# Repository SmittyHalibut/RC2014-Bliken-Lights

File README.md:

# RC2014-Bliken-Lights
A Blinken Lights front panel for the RC2014.

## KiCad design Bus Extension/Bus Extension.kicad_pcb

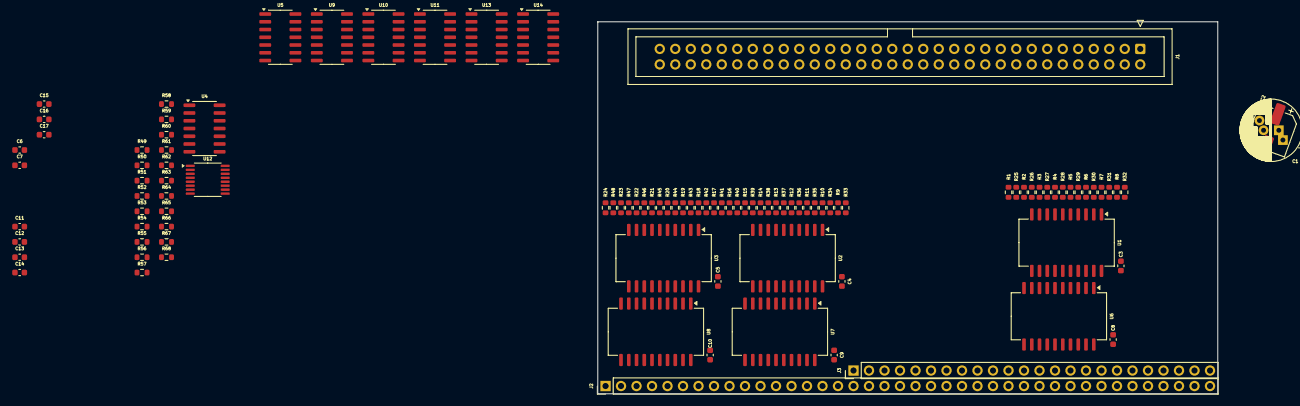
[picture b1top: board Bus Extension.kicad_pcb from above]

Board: 2 copper layers, 101.6 x 61.0 mm, 102 parts (0 on the bottom side), 146 nets, no tracks yet.

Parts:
C1: 100uF; CP_Radial_D10.0mm_P2.50mm_P5.00mm
C2: 100uF; CP_Elec_6.3x5.4
C3, C4, C5, C6, C7, C8, C9, C10, C11, C12, C13, C14, C15, C16, C17: 1uF; C_0603_1608Metric
J1: Conn_02x32_Row_Letter_First; IDC-Header_2x32_P2.54mm_Vertical
J2: Conn_01x40; PinHeader_1x40_P2.54mm_Vertical
J3: Conn_01x24; PinHeader_1x24_P2.54mm_Vertical
R1, R2, R3, R4, R5, R6, R7, R8, R9, R10, R11, R12, R13, R14, R15, R16, R17, R18, R19, R20, R21, R22, R23, R24, R49, R50, R51, R52, R53, R54, R55, R56, R57, R58, R59, R60: 470R; R_0603_1608Metric
R25, R26, R27, R28, R29, R30, R31, R32, R33, R34, R35, R36, R37, R38, R39, R40, R41, R42, R43, R44, R45, R46, R47, R48, R61, R62, R63, R64, R65, R66, R67, R68: 10k; R_0603_1608Metric
U1, U2, U3, U6, U7, U8: 74HCT244; SOIC-20W_7.5x15.4mm_P1.27mm
U4, U5: 74HCT02; SOIC-14_3.9x8.7mm_P1.27mm
U9, U10: 74HCT04; SOIC-14_3.9x8.7mm_P1.27mm
U11: 74HC74; SOIC-14_3.9x8.7mm_P1.27mm
U12: 74HC123; TSSOP-16_4.4x5mm_P0.65mm
U13, U14: 74LS125; SOIC-14_3.9x8.7mm_P1.27mm

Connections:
+5V: C1.1, C2.1, C3.1, C4.1, C5.1, C6.1, C7.1, C8.1, C9.1, C10.1, C11.1, C12.1, C13.1, C15.1, C16.1, C17.1, J2.18, J3.2, R25.2, R26.2, R27.2, R28.2, R29.2, R30.2, R31.2, R32.2, R33.2, R34.2, R35.2, R36.2, R37.2, R38.2, R39.2, R40.2, R41.2, R42.2, R43.2, R44.2, R45.2, R46.2, R47.2, R48.2, R49.1, R61.2, R62.2, R63.2, R64.2, R65.2, R66.2, R67.2, R68.1, U1.20 (VCC), U2.20 (VCC), U3.20 (VCC), U4.14 (VCC), U5.14 (VCC), U6.20 (VCC), U7.20 (VCC), U8.20 (VCC), U9.14 (VCC), U10.14 (VCC), U11.2 (D), U11.4 (~S), U11.14 (VCC), U12.10 (B), U12.11 (Clr), U12.16 (VCC), U13.14 (VCC), U14.14 (VCC)
/A0: J2.16, U2.2 (1A0), U7.18 (1Y0)
/A1: J2.15, U2.17 (2A0), U7.3 (2Y0)
/A2: J2.14, U2.4 (1A1), U7.16 (1Y1)
/A3: J2.13, U2.15 (2A1), U7.5 (2Y1)
/A4: J2.12, U2.6 (1A2), U7.14 (1Y2)
/A5: J2.11, U2.13 (2A2), U7.7 (2Y2)
/A6: J2.10, U2.8 (1A3), U7.12 (1Y3)
/A7: J2.9, U2.11 (2A3), U7.9 (2Y3)
/A8: J2.8, U3.2 (1A0), U8.18 (1Y0)
/A9: J2.7, U3.17 (2A0), U8.3 (2Y0)
/A10: J2.6, U3.4 (1A1), U8.16 (1Y1)
/A11: J2.5, U3.15 (2A1), U8.5 (2Y1)
/A12: J2.4, U3.6 (1A2), U8.14 (1Y2)
/A13: J2.3, U3.13 (2A2), U8.7 (2Y2)
/A14: J2.2, U3.8 (1A3), U8.12 (1Y3)
/A15: J2.1, U3.11 (2A3), U8.9 (2Y3)
/BUSAK: U5.3, U9.1
/BUSRQ: J3.8, U13.3
/BUSRQSW: J1.48, R64.1, U5.2, U13.1
/D0: J2.27, U1.11 (2A3), U6.9 (2Y3)
/D1: J2.28, U1.8 (1A3), U6.12 (1Y3)
/D2: J2.29, U1.13 (2A2), U6.7 (2Y2)
/D3: J2.30, U1.6 (1A2), U6.14 (1Y2)
/D4: J2.31, U1.15 (2A1), U6.5 (2Y1)
/D5: J2.32, U1.4 (1A1), U6.16 (1Y1)
/D6: J2.33, U1.17 (2A0), U6.3 (2Y0)
/D7: J2.34, U1.2 (1A0), U6.18 (1Y0)
/DBUSSW: J1.52, R61.1, U5.8
/DBUS_EN: U5.10, U9.13, U13.4
/HALT: J3.7, U9.3
/HAVEBUS: U5.1, U10.5
/LED A0: J1.3, R9.2
/LED A1: J1.7, R10.2
/LED A2: J1.11, R11.2
/LED A3: J1.15, R12.2
/LED A4: J1.19, R13.2
/LED A5: J1.23, R14.2
/LED A6: J1.27, R15.2
/LED A7: J1.31, R16.2
/LED A8: J1.33, R17.2
/LED A9: J1.37, R18.2
/LED A10: J1.41, R19.2
/LED A11: J1.45, R20.2
/LED A12: J1.49, R21.2
/LED A13: J1.53, R22.2
/LED A14: J1.57, R23.2
/LED A15: J1.61, R24.2
/LED D0: J1.2, R1.2
/LED D1: J1.4, R2.2
/LED D2: J1.6, R3.2
/LED D3: J1.8, R4.2
/LED D4: J1.10, R5.2
/LED D5: J1.12, R6.2
/LED D6: J1.14, R7.2
/LED D7: J1.16, R8.2
/LED IORD: J1.38, R53.2
/LED IOWR: J1.40, R54.2
/LED MEMRD: J1.34, R51.2
/LED MEMRW: J1.36, R52.2
/LED Power: J1.60, R49.2
/LED ~BUSAK: J1.46, R50.2
/LED ~HALT: J1.42, R56.2
/LED ~WAIT: J1.44, R55.2
/M1: J2.19, U12.9 (A)
/MEMIOSW: J1.54, R62.1, U10.13, U14.2
/Reset: J1.62, J2.20, R65.1
/SINGLESW: J1.56, R63.1, U5.11
/STEPSW: J1.58, R66.1, U11.3 (C)
/SW A0: J1.1, R33.1, U7.2 (1A0)
/SW A1: J1.5, R34.1, U7.17 (2A0)
/SW A2: J1.9, R35.1, U7.4 (1A1)
/SW A3: J1.13, R36.1, U7.15 (2A1)
/SW A4: J1.17, R37.1, U7.6 (1A2)
/SW A5: J1.21, R38.1, U7.13 (2A2)
/SW A6: J1.25, R39.1, U7.8 (1A3)
/SW A7: J1.29, R40.1, U7.11 (2A3)
/SW A8: J1.35, R41.1, U8.2 (1A0)
/SW A9: J1.39, R42.1, U8.17 (2A0)
/SW A10: J1.43, R43.1, U8.4 (1A1)
/SW A11: J1.47, R44.1, U8.15 (2A1)
/SW A12: J1.51, R45.1, U8.6 (1A2)
/SW A13: J1.55, R46.1, U8.13 (2A2)
/SW A14: J1.59, R47.1, U8.8 (1A3)
/SW A15: J1.63, R48.1, U8.11 (2A3)
/SW D0: J1.18, R25.1, U6.11 (2A3)
/SW D1: J1.20, R26.1, U6.8 (1A3)
/SW D2: J1.22, R27.1, U6.13 (2A2)
/SW D3: J1.24, R28.1, U6.6 (1A2)
/SW D4: J1.26, R29.1, U6.15 (2A1)
/SW D5: J1.28, R30.1, U6.4 (1A1)
/SW D6: J1.30, R31.1, U6.17 (2A0)
/SW D7: J1.32, R32.1, U6.2 (1A0)
/SW WRITE: J1.50, R67.1, U5.5
/WAIT: U9.5, U13.11
/WAITING: U10.8, U13.13
/WRITING: U5.4, U10.11
/~BUSAK: R50.1, U9.2
/~DBUS_EN: U5.6, U6.1 (1OE), U6.19 (2OE), U9.12
/~HALT: R56.1, U9.4
/~HAVEBUS: U5.9, U7.1 (1OE), U7.19 (2OE), U8.1 (1OE), U8.19 (2OE), U10.6, U14.1, U14.4
/~MEMIOSW: U10.12, U14.5
/~RX2: R60.1, U10.4
/~RX: R58.1, U9.10
/~TX2: R59.1, U10.2
/~TX: R57.1, U9.8
/~WAIT: R55.1, U9.6
/~WRITING: U10.10, U13.10
GND: C1.2, C2.2, C3.2, C4.2, C5.2, C6.2, C7.2, C8.2, C9.2, C10.2, C11.2, C12.2, C13.2, C15.2, C16.2, C17.2, J1.64, J2.17, J3.1, U1.1 (1OE), U1.10 (GND), U1.19 (2OE), U2.1 (1OE), U2.10 (GND), U2.19 (2OE), U3.1 (1OE), U3.10 (GND), U3.19 (2OE), U4.7 (GND), U5.7 (GND), U6.10 (GND), U7.10 (GND), U8.10 (GND), U9.7 (GND), U10.7 (GND), U11.7 (GND), U12.8 (GND), U13.2, U13.5, U13.7 (GND), U13.9, U13.12, U14.7 (GND), U14.9, U14.10, U14.12, U14.13
IORD: R53.1, U4.10
IORQ: J2.26, U4.8, U4.11, U14.6
IOWR: R54.1, U4.13
MEMRD: R51.1, U4.1
MEMWR: R52.1, U4.4
MREQ: U4.2, U4.5, U14.3
unnamed: R8.1, U1.18 (1Y0)
unnamed: R6.1, U1.16 (1Y1)
unnamed: R4.1, U1.14 (1Y2)
unnamed: R2.1, U1.12 (1Y3)
unnamed: R7.1, U1.3 (2Y0)
unnamed: R5.1, U1.5 (2Y1)
unnamed: R3.1, U1.7 (2Y2)
unnamed: R1.1, U1.9 (2Y3)
unnamed: R9.1, U2.18 (1Y0)
unnamed: R11.1, U2.16 (1Y1)
unnamed: R13.1, U2.14 (1Y2)
unnamed: R15.1, U2.12 (1Y3)
unnamed: R10.1, U2.3 (2Y0)
unnamed: R12.1, U2.5 (2Y1)
unnamed: R14.1, U2.7 (2Y2)
unnamed: R16.1, U2.9 (2Y3)
unnamed: R17.1, U3.18 (1Y0)
unnamed: R19.1, U3.16 (1Y1)
unnamed: R21.1, U3.14 (1Y2)
unnamed: R23.1, U3.12 (1Y3)
unnamed: R18.1, U3.3 (2Y0)
unnamed: R20.1, U3.5 (2Y1)
unnamed: R22.1, U3.7 (2Y2)
unnamed: R24.1, U3.9 (2Y3)
unnamed: U5.13, U10.9
unnamed: U5.12, U11.5 (Q)
unnamed: U11.1 (~R), U12.12 (~Q)
unnamed: C14.2, U12.6 (Cext)
unnamed: C14.1, R68.2, U12.7 (RCext)
RD: U4.3, U4.9, U13.6
WR: U4.6, U4.12, U13.8

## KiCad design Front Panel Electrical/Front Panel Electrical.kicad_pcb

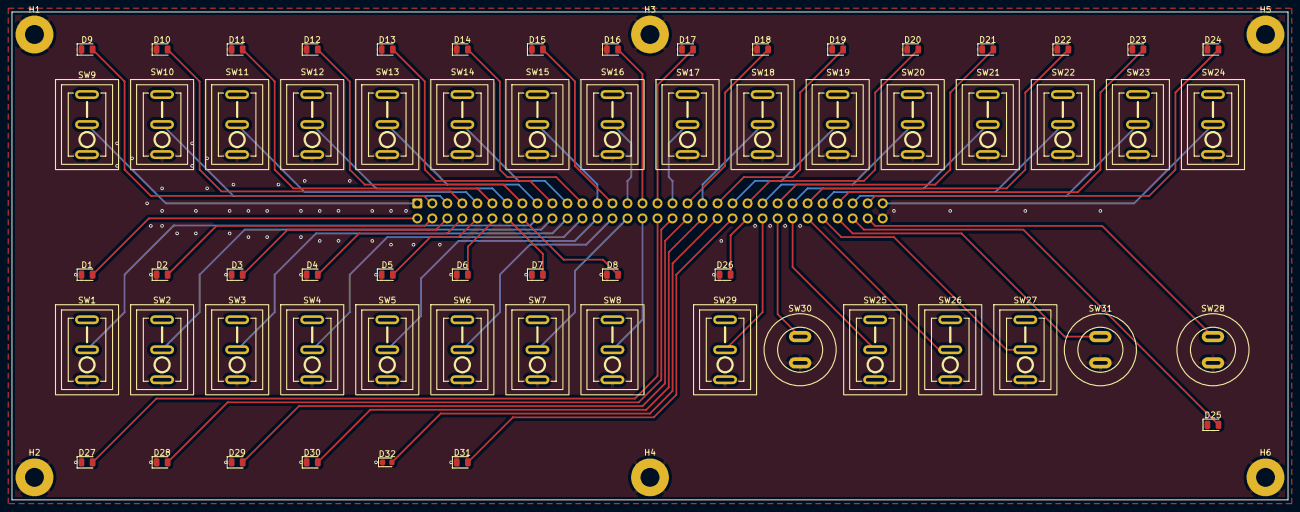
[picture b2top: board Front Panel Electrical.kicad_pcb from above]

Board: 2 copper layers, 215.9 x 82.6 mm, 70 parts (1 on the bottom side), 64 nets.

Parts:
D1, D2, D3, D4, D5, D6, D7, D8, D9, D10, D11, D12, D13, D14, D15, D16, D17, D18, D19, D20, D21, D22, D23, D24, D26, D27, D28, D29, D30, D31: Yellow; LED_0805_2012Metric
D25: Green; LED_0805_2012Metric
D32: Red LED; LED_0603_1608Metric
H1, H2, H3, H4, H5, H6: MountingHole_Pad; MountingHole_3.2mm_M3_Pad
J2: Conn_02x32_Row_Letter_First; IDC-Header_2x32_P2.54mm_Vertical
SW1, SW2, SW3, SW4, SW9, SW10, SW11, SW12, SW17, SW18, SW19, SW20: Black; Switch_Rocker_SPDT_15x10mm
SW5, SW6, SW7, SW8, SW13, SW14, SW15, SW16, SW21, SW22, SW23, SW24: Red; Switch_Rocker_SPDT_15x10mm
SW25, SW26, SW27, SW29: Switch; Switch_Rocker_SPDT_15x10mm
SW28, SW30, SW31: Button; Switch_Pushbutton_SPST_12mm

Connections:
/LED A0: D9.2 (A), J2.3
/LED A1: D10.2 (A), J2.7
/LED A2: D11.2 (A), J2.11
/LED A3: D12.2 (A), J2.15
/LED A4: D13.2 (A), J2.19
/LED A5: D14.2 (A), J2.23
/LED A6: D15.2 (A), J2.27
/LED A7: D16.2 (A), J2.31
/LED A8: D17.2 (A), J2.33
/LED A9: D18.2 (A), J2.37
/LED A10: D19.2 (A), J2.41
/LED A11: D20.2 (A), J2.45
/LED A12: D21.2 (A), J2.49
/LED A13: D22.2 (A), J2.53
/LED A14: D23.2 (A), J2.57
/LED A15: D24.2 (A), J2.61
/LED D0: D1.2 (A), J2.2
/LED D1: D2.2 (A), J2.4
/LED D2: D3.2 (A), J2.6
/LED D3: D4.2 (A), J2.8
/LED D4: D5.2 (A), J2.10
/LED D5: D6.2 (A), J2.12
/LED D6: D7.2 (A), J2.14
/LED D7: D8.2 (A), J2.16
/LED IORD: D29.2 (A), J2.38
/LED IOWR: D30.2 (A), J2.40
/LED MEMRD: D27.2 (A), J2.34
/LED MEMRW: D28.2 (A), J2.36
/LED Power: D25.2 (A), J2.60
/LED ~BUSAK: D26.2 (A), J2.46
/LED ~HALT: D32.2 (A), J2.42
/LED ~WAIT: D31.2 (A), J2.44
/SW A0: J2.1, SW9.2 (B)
/SW A1: J2.5, SW10.2 (B)
/SW A2: J2.9, SW11.2 (B)
/SW A3: J2.13, SW12.2 (B)
/SW A4: J2.17, SW13.2 (B)
/SW A5: J2.21, SW14.2 (B)
/SW A6: J2.25, SW15.2 (B)
/SW A7: J2.29, SW16.2 (B)
/SW A8: J2.35, SW17.2 (B)
/SW A9: J2.39, SW18.2 (B)
/SW A10: J2.43, SW19.2 (B)
/SW A11: J2.47, SW20.2 (B)
/SW A12: J2.51, SW21.2 (B)
/SW A13: J2.55, SW22.2 (B)
/SW A14: J2.59, SW23.2 (B)
/SW A15: J2.63, SW24.2 (B)
/SW BUSRQ: J2.48, SW29.2 (B)
/SW D0: J2.18, SW1.2 (B)
/SW D1: J2.20, SW2.2 (B)
/SW D2: J2.22, SW3.2 (B)
/SW D3: J2.24, SW4.2 (B)
/SW D4: J2.26, SW5.2 (B)
/SW D5: J2.28, SW6.2 (B)
/SW D6: J2.30, SW7.2 (B)
/SW D7: J2.32, SW8.2 (B)
/SW DBUS: J2.52, SW25.2 (B)
/SW MEMIO: J2.54, SW26.2 (B)
/SW Reset: J2.62, SW28.2 (B)
/SW SINGLE: J2.56, SW27.2 (B)
/SW STEP: J2.58, SW31.2 (B)
/SW WRITE: J2.50, SW30.2 (B)
GND: D1.1 (K), D2.1 (K), D3.1 (K), D4.1 (K), D5.1 (K), D6.1 (K), D7.1 (K), D8.1 (K), D9.1 (K), D10.1 (K), D11.1 (K), D12.1 (K), D13.1 (K), D14.1 (K), D15.1 (K), D16.1 (K), D17.1 (K), D18.1 (K), D19.1 (K), D20.1 (K), D21.1 (K), D22.1 (K), D23.1 (K), D24.1 (K), D25.1 (K), D26.1 (K), D27.1 (K), D28.1 (K), D29.1 (K), D30.1 (K), D31.1 (K), D32.1 (K), H1.1, H2.1, H3.1, H4.1, H5.1, H6.1, J2.64, SW1.1 (A), SW2.1 (A), SW3.1 (A), SW4.1 (A), SW5.1 (A), SW6.1 (A), SW7.1 (A), SW8.1 (A), SW9.1 (A), SW10.1 (A), SW11.1 (A), SW12.1 (A), SW13.1 (A), SW14.1 (A), SW15.1 (A), SW16.1 (A), SW17.1 (A), SW18.1 (A), SW19.1 (A), SW20.1 (A), SW21.1 (A), SW22.1 (A), SW23.1 (A), SW24.1 (A), SW25.1 (A), SW26.1 (A), SW27.1 (A), SW28.1 (A), SW29.1 (A), SW30.1 (A), SW31.1 (A)

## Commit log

2024-09-25 First whack. Still a WIP
